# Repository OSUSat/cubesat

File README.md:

# Oregon State University (OSU) AIAA OSUSat/SCRT Climate Science CubeSat

Welcome to the central repository for the **OSUSat Climate Science CubeSat** project. This repository contains the hardware designs, firmware, and documentation for the sub-systems comprising the satellite.

---

## Mission Context & Goals

The **OSUSat Climate Science CubeSat** is a low-Earth orbit (LEO) satellite designed to capture high-resolution imagery and scientific data for climate science research. 

### Mission Objectives

1. **Earth Observations**: Capture multispectral or high-resolution imagery using a dual-camera payload to study surface health, atmospheric conditions, cloud formations.
2. **Reliable Power Delivery (EPS)**: Harvest solar power from 6 body-mounted solar panels, manage charge for 4x 18650 Li-ion batteries, and distribute and regulate power rails to prevent overcurrent/overvoltage events.
3. **Command & Telemetry (OBC)**: Orchestrate system operations, manage communication buses (CANBus, UART, I2C, SPI), process ground commands, and monitor satellite health.

---

## System Architecture

The satellite is divided into five primary subsystems interconnected via a shared backplane connector (exposing power rails and UART/CAN control buses):

```mermaid
graph TD
    Solar[Solar Panels & Batteries] --> EPS[Electrical Power System - EPS]

    EPS -->|Power| OBC[On-Board Computer - OBC]
    EPS -->|Power| Payload[Science Camera Payload]
    EPS -->|Power| ADCS[Attitude Determination & Control - ADCS]
    EPS -->|Power| Comms[UHF Communications]

    OBC <-->|Control Bus| EPS
    OBC <-->|Control Bus| Payload
    OBC <-->|Control Bus| ADCS
    OBC <-->|Control Bus| Comms

    Comms <-->|Radio Link| Ground[Ground Station]
```

### 1. Electrical Power System (EPS)

* **Microcontroller**: NXP S32K3 Series / STM32L496xx (ARM Cortex-M4)
* **Responsibilities**:
    * Solar energy harvesting with Maximum Power Point Tracking (MPPT).
    * Battery charge/discharge management (2 independent packs of 2x 18650 cells).
    * Voltage regulation (3.3V & 5V rails) with software-controllable load switches.
    * Fast hardware-level and software-level overcurrent protection.
    * Hardware watchdog monitoring.
    * Broad mission context management using the MCU

### 2. On-Board Computer (OBC)

* **Microcontroller**: Main MCU + STM32H743xx (ARM Cortex-M7)
* **Responsibilities**:
    * Master command parsing and state management.
    * Health heartbeats and telemetry collection.
    * Orbital calculations and scheduling payload imaging windows.
    * Ground station radio communication interface.

### 3. Payload

* **Processor**: Raspberry Pi Compute Module 4 (CM4)
* **Responsibilities**:
    * High-speed dual-camera scientific imaging.
    * Actuator/motor driver control (e.g., lens shutters, filter wheels) (V1 Only).
    * Image compression and storage before downlink.

### 4. Attitude Determination and Control System (ADCS)

* **Responsibilities**: Detumbling the spacecraft, aligning the imaging payload to nadir pointing, and tracking target orientations.

### 5. UHF Communications (Comms)

* **Responsibilities**: Uplinking commands and telemetry requests from ground stations, and downlinking collected science data and telemetry beacons.

---

## Repository Structure

The project uses a versioned directory structure separating hardware and firmware iterations:

```
.
├── .github/                     # GitHub Workflows & Issue/PR Templates
│   └── workflows/
│       ├── build_and_docs.yml   # CI/CD action defining the pipeline
│       └── build_and_test.sh    # Dynamic build script runner
│
├── adcs/                        # Attitude Determination and Control System
│   ├── v1/
│   └── v2/
│
├── eps/                         # Electrical Power System Subsystem
│   ├── v1/                      # Version 1 (Prototype Model)
│   │   ├── firmware/            # STM32L4 firmware (CMake, CUnit tests, mocks)
│   │   ├── hardware/            # KiCad schematic, layout, symbols, & footprints
│   │   └── documentation/       # Doxygen, Sphinx configuration & spec files
│   ├── v2/                      # Version 2 (Placeholder for v2 development)
│   └── documentation/           # Bootflows, subsystem specifications, & kickoff info
│
├── obc/                         # On-Board Computer Subsystem
│   ├── v1/                      # Version 1 (Prototype Model)
│   │   ├── firmware/            # STM32H7 firmware (CMake)
│   │   ├── hardware/            # KiCad schematic and layout
│   │   └── tests/               # Pico-based LoRa packet transmission test
│   ├── v2/                      # Version 2 (Placeholder for v2 development)
│   └── documentation/           # OBC specific documentation
│
├── payload/                     # Science Camera Payload
│   ├── v1/                      # Version 1 (Prototype Model)
│   │   └── hardware/            # KiCad CM4 baseboard schematic and layout
│   ├── v2/                      # Version 2 (Placeholder for v2 development)
│   └── documentation/           # Payload specific documentation
│
├── comms/                       # UHF Communications Subsystem (Planned)
│   ├── v1/
│   └── v2/
│
└── documentation/               # Global guidelines & Quality Assurance process
    ├── checklists/              # Bringup, layout, schematic & firmware service templates
    └── design_guidelines/       # Writing ATPs, Hardware Design, HITL, Polling/Interrupts
```

---

## Getting Started & Building

### 1. Prerequisite Toolchains

Ensure you have the following installed on your host system:
* **ARM Cross Compiler**: `gcc-arm-none-eabi`
* **Build System Tools**: `cmake`, `make`, `g++`
* **Documentation Generators**: `doxygen`, Python 3 + `sphinx`

### 2. Fetching Submodules

This repository utilizes submodules (such as `osusat/core` and `osusat/messaging`). Clone with submodules or initialize them:
```bash
git submodule update --init --recursive
```

### 3. Hardware Development & KiCad Templates

To create new expansion / daughterboard hardware designs in KiCad, symlink the shared template directory to your local KiCad user template path:

- **Linux**:
  ```bash
  mkdir -p ~/.local/share/kicad/10.0/template
  ln -sf /path/to/cubesat/repo/shared/kicad/templates/test_board ~/.local/share/kicad/10.0/template/test_board
  ```
- **Windows (PowerShell)**:
  ```powershell
  New-Item -ItemType Directory -Force -Path "$env:APPDATA\kicad\10.0\template"
  New-Item -ItemType SymbolicLink -Path "$env:APPDATA\kicad\10.0\template\test_board" -Target "C:\path\to\cubesat\repo\shared\kicad\templates\test_board"
  ```

Once symlinked, open KiCad, click **File → New Project from Template...**, select the **User Templates** tab, and choose **OSUSat Backplane Test Board Template**.

For full manual setup options and details, see [shared/kicad/README.md](./shared/kicad/README.md).

### 4. Compilation Guide

#### Building for the ARM Target (e.g., EPS v1)

To build the firmware binaries to flash onto the MCU:

```bash
cd eps/v1/firmware
cmake -B build_arm -S . -DCMAKE_TOOLCHAIN_FILE=arm-none-eabi-toolchain.cmake
cmake --build build_arm
```

*Outputs: `.elf`, `.hex`, and `.bin` files will be generated under `build_arm/`.*

#### Building Host Tests / Hardware-in-the-Loop (HITL) Mocks

To build and execute unit tests on your local machine:

```bash
cd eps/v1/firmware
cmake -B build_hitl -S . -DTARGET_ARCH=HOST -DBUILD_HITL=ON
cmake --build build_hitl
cd build_hitl && ctest --output-on-failure
```

---

## CI/CD Pipeline

The repository uses a generalized GitHub Actions workflow:
* **Scope-Based Execution**: Uses git diffs to detect which subsystem version has been modified (e.g. `eps/v1/` vs `obc/v1/`) and builds only the affected firmware.
* **Continuous Integration**: Runs host-based CTests automatically to verify changes.
* **Documentation Deployments**: Generates Doxygen API listings and Sphinx documentation on successful builds. Pull Requests automatically receive a comment with links to Pages-hosted previews of the documentation.

---

## Quality Assurance & Contributions

Before submitting a Pull Request, contributors must follow the project's QA procedures found in `/documentation`:

1. **Issue Checkout:** Before work or contributions begin, ensure your changes are encapsulated by an issue in the GitHub project
2. **Design Guidelines:** For any and all changes, follow the [design guidelines.](./documentation/design_guidelines/)
3. **Design Reviews**: Complete the [Schematic Review Checklist](./documentation/checklists/schematic_review.md) and [Layout Review Checklist](./documentation/checklists/layout_review.md) checklists before fabricating PCBs.
4. **Firmware Guidelines**: Adhere to the [HITL Guidelines](./documentation/design_guidelines/hitl.md) and [Keeping the HAL Policy Free](./documentation/design_guidelines/keeping_the_hal_policy_free.md) design rules.
5. **Acceptance Tests**: All hardware deliverables require a formal [ATP (Acceptance Test Procedure)](./documentation/design_guidelines/writing_atps.md).

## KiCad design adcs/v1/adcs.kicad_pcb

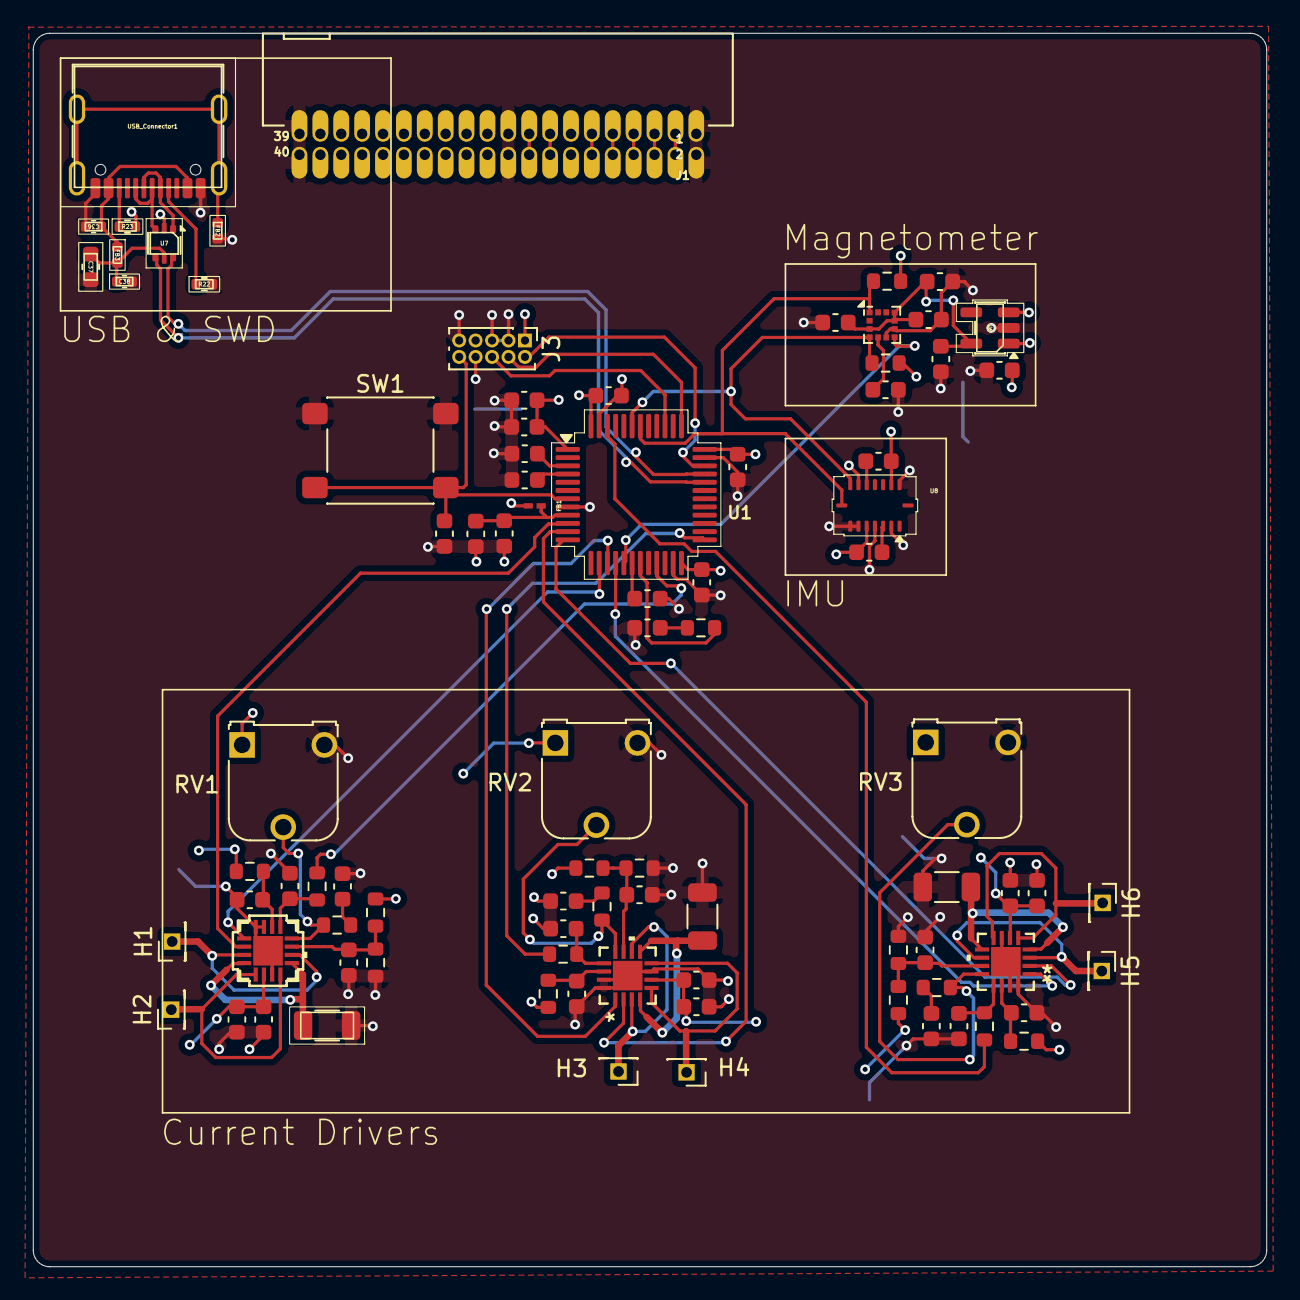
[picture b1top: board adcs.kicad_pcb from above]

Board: 4 copper layers, 75.0 x 75.0 mm, 88 parts (0 on the bottom side), 68 nets.

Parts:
C1: 4.7u; C_0603_1608Metric
C2, C3: 10p; C_0603_1608Metric
C4, C5: 20p; C_0603_1608Metric
C6, C8, C9, C11, C19, C20, C39, C40, C41: 100n; C_0603_1608Metric
C7: 0.1uF; C_0603_1608Metric
C10, C18, C34, C35, C37: 1u; C_0603_1608Metric
C12, C22, C28: 1n; C_0603_1608Metric
C13, C23, C29: 10n; C_0603_1608Metric
C14, C15, C24, C25, C30, C31: 22n; C_0603_1608Metric
C16, C26, C32: 2.2u; C_0603_1608Metric
C17, C27, C33: 22u; C_0603_1608Metric
C21: 220n; C_0603_1608Metric
C36: 10n; C_0402_1005Metric
C38: 100n; C_0402_1005Metric
FB1: 120R; IND_BLM03_0201_MUR
FB2, FB3: 120R; L_0402_1005Metric
H1, H2, H3, H4, H5, H6: MountingHole_Pad; PinHeader_1x01_P1.27mm_Vertical
J1: Conn_02x20_Counter_Clockwise; J-SAMTEC-TFM-120-X1-XXX-D-RA
J3: Conn_ARM_JTAG_SWD_10; PinHeader_2x05_P1.00mm_Vertical
R1: 390; R_0603_1608Metric
R2, R6, R10, R14, R16, R20: 1k; R_0603_1608Metric
R3, R11, R17: 10k; R_0603_1608Metric
R4, R5, R12, R13, R18, R19: 18k; R_0603_1608Metric
R7, R15, R21: 330m; R_1206_3216Metric
R8, R9: 4.7k; R_0603_1608Metric
R22, R23: 5.1k; R_0402_1005Metric
RV1, RV2, RV3: R_Potentiometer_Trim_US; Potentiometer_Runtron_RM-065_Vertical
SW1: SW_Push; SW_SPST_PTS645Sx43SMTR92
U1: STM32L4Q5CGTx; LQFP-48_7x7mm_P0.5mm
U2, U4, U5: STSPIN250; VFQFPN16_STSPIN_STM
U3: LIS2MDL; LGA-12_2x2mm_P0.5mm
U6: AP2112K-1.2; SOT-23-5
U7: USBLC6-2P6; SOT-666
U8: BMI088; Bosch_LGA-16_4.5x3mm_P0.5mm_LayoutBorder7x1y_ClockwisePinNu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
USB_Connector1: USB_C_Receptacle_USB2.0_16P; USB_C_Receptacle_G-Switch_GT-USB-7010ASV

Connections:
+1V8: C18.1, C19.1, C20.1, C35.1, U3.3 (~CS), U3.9 (Vdd), U3.10 (Vdd_IO), U6.5 (VOUT)
+3V3: C1.1, C6.1, C8.1, C9.1, C16.1, C17.1, C26.1, C27.1, C32.1, C33.1, C34.1, C39.1, C40.1, C41.1, FB1.1, J1.13, J1.14, J3.1 (VTref), R2.1, R5.1, R8.1, R9.1, R10.1, R13.1, R16.1, R19.1, RV1.1, RV2.1, RV3.1, U1.1 (VBAT), U1.24 (VDD), U1.36 (VDDUSB), U1.48 (VDD), U2.6 (VS), U4.6 (VS), U5.6 (VS), U6.1 (VIN), U6.3 (EN), U8.5 (~CSB2), U8.14 (~CSB1)
/EN1: R4.2, U1.21 (PB10)
/EN2: R12.2, U1.25 (PB12)
/EN3: R18.2, U1.46 (PB9)
/I2C1_SCL: R9.2, U1.42 (PB6), U3.1 (SCL/SPC), U8.8 (SCK/SCL)
/I2C1_SDA: R8.2, U1.43 (PB7), U3.4 (SDA/SDI/SDO), U8.9 (SDI/SDA)
/Inter-Board Connector/RAIL_1_VOUT: J1.3, J1.4
/Inter-Board Connector/RAIL_2_VOUT: J1.5, J1.6
/Inter-Board Connector/RAIL_3_VOUT: J1.7, J1.8
/Inter-Board Connector/RAIL_4_VOUT: J1.9, J1.10
/Inter-Board Connector/RAIL_5_VOUT: J1.11, J1.12
/Inter-Board Connector/RAIL_7_VOUT: J1.15, J1.16
/Inter-Board Connector/RAIL_8_VOUT: J1.17, J1.18
/MNT_INT: U1.17 (PA7), U3.7 (DRDY)
/PC14-OSC32_IN: C2.1, U1.3 (PC14)
/PC15-OSC32_OUT: C3.1, U1.4 (PC15)
/PH1: U1.14 (PA4), U2.1 (PH)
/PH2: U1.15 (PA5), U4.1 (PH)
/PH3: U1.16 (PA6), U5.1 (PH)
/PWM1_TIM2_CH1: U1.10 (PA0), U2.2 (PWM)
/PWM2_TIM2_CH2: U1.11 (PA1), U4.2 (PWM)
/PWM2_TIM2_CH3: U1.12 (PA2), U5.2 (PWM)
/STSPIN Current Driver1/V_REF: C14.1, R2.2, R3.1, U2.11 (REF)
/STSPIN Current Driver2/V_REF: C24.1, R10.2, R11.1, U4.11 (REF)
/STSPIN Current Driver3/V_REF: C30.1, R16.2, R17.1, U5.11 (REF)
/SWCLK: J3.4 (SWCLK/TCK), U1.37 (PA14)
/SWDIO: J3.2 (SWDIO/TMS), U1.34 (PA13)
/SWO: J3.6 (SWO/TDO), U1.39 (PB3)
/USB-C/CC1: R22.1, USB_Connector1.A5 (CC1)
/USB-C/CC2: R23.1, USB_Connector1.B5 (CC2)
/USB-C/FB: FB2.1, USB_Connector1.SH (SHIELD)
/USB-C/PI: C36.1, FB3.1, USB_Connector1.A4 (VBUS), USB_Connector1.A9 (VBUS), USB_Connector1.B4 (VBUS), USB_Connector1.B9 (VBUS)
/USB-C/UNPROT_USB_D+: U7.3 (I/O2), USB_Connector1.A6 (D+), USB_Connector1.B6 (D+)
/USB-C/UNPROT_USB_D-: U7.1 (I/O1), USB_Connector1.A7 (D-), USB_Connector1.B7 (D-)
/USBC-D+: U1.33 (PA12), U7.6 (I/O1)
/USBC-D-: U1.32 (PA11), U7.4 (I/O2)
/VDDA: C10.1, C11.1, FB1.2, U1.9 (VDDA)
/nRST: C7.1, J3.10 (~RESET), SW1.2, U1.7 (NRST)
GND: C1.2, C2.2, C3.2, C4.2, C5.2, C6.2, C7.2, C8.2, C9.2, C10.2, C11.2, C12.2, C13.2, C14.2, C15.2, C16.2, C17.2, C18.2, C19.2, C20.2, C21.2, C22.2, C23.2, C24.2, C25.2, C26.2, C27.2, C28.2, C29.2, C30.2, C31.2, C32.2, C33.2, C34.2, C35.2, C36.2, C37.2, C38.2, C41.2, FB2.2, J1.1, J1.2, J1.19, J1.20, J1.39, J1.40, J3.3 (GND), J3.5 (GND), J3.8 (NC/TDI), J3.9 (GNDDetect), R3.2, R7.1, R11.2, R15.1, R17.2, R21.1, R22.2, R23.2, RV1.3, RV2.3, RV3.3, SW1.1, U1.8 (VSSA), U1.23 (VSS), U1.35 (VSS), U1.47 (VSS), U2.7 (GND), U2.15 (TEST0), U2.16 (TEST1), U2.17 (EPAD), U3.6 (GND), U3.8 (GND), U4.7 (GND), U4.15 (TEST0), U4.16 (TEST1), U4.17 (EPAD), U5.7 (GND), U5.15 (TEST0), U5.16 (TEST1), U5.17 (EPAD), U6.2 (GND), U7.2 (GND), U8.2 (GNDA), U8.4 (GNDA), U8.6 (GNDIO), U8.7 (PS), U8.10 (SDO2), U8.15 (SDO1), USB_Connector1.A1 (GND), USB_Connector1.A12 (GND), USB_Connector1.B1 (GND), USB_Connector1.B12 (GND)
unnamed: C4.1, R1.1
unnamed: C15.1, R6.2
unnamed: C25.1, R14.2
unnamed: C31.1, R20.2
unnamed: C5.1, U1.18 (PB0)
unnamed: R1.2, U1.19 (PB1)
unnamed: C13.1, R4.1, U2.13 (EN/FAULT)
unnamed: H1.1 (1_1), U2.3 (OUTA1), U2.10 (OUTB1)
unnamed: H2.1 (1_1), U2.5 (OUTA2), U2.8 (OUTB2)
unnamed: R7.2, U2.4 (SENSEA), U2.9 (SENSEB)
unnamed: C12.1, R5.2, U2.14 (STBY/RESET)
unnamed: R6.1, RV1.2, U2.12 (TOFF)
unnamed: C21.1, U3.5 (C1)
unnamed: C23.1, R12.1, U4.13 (EN/FAULT)
unnamed: H3.1 (1_1), U4.3 (OUTA1), U4.10 (OUTB1)
unnamed: H4.1 (1_1), U4.5 (OUTA2), U4.8 (OUTB2)
unnamed: R15.2, U4.4 (SENSEA), U4.9 (SENSEB)
unnamed: C22.1, R13.2, U4.14 (STBY/RESET)
unnamed: R14.1, RV2.2, U4.12 (TOFF)
unnamed: C29.1, R18.1, U5.13 (EN/FAULT)
unnamed: H5.1 (1_1), U5.3 (OUTA1), U5.10 (OUTB1)
unnamed: H6.1 (1_1), U5.5 (OUTA2), U5.8 (OUTB2)
unnamed: R21.2, U5.4 (SENSEA), U5.9 (SENSEB)
unnamed: C28.1, R19.2, U5.14 (STBY/RESET)
unnamed: R20.1, RV3.2, U5.12 (TOFF)
unnamed: C39.2, U8.3 (VDD)
unnamed: C40.2, U8.11 (VDDIO)
VBUS: C37.1, C38.1, FB3.2, U7.5 (VBUS)

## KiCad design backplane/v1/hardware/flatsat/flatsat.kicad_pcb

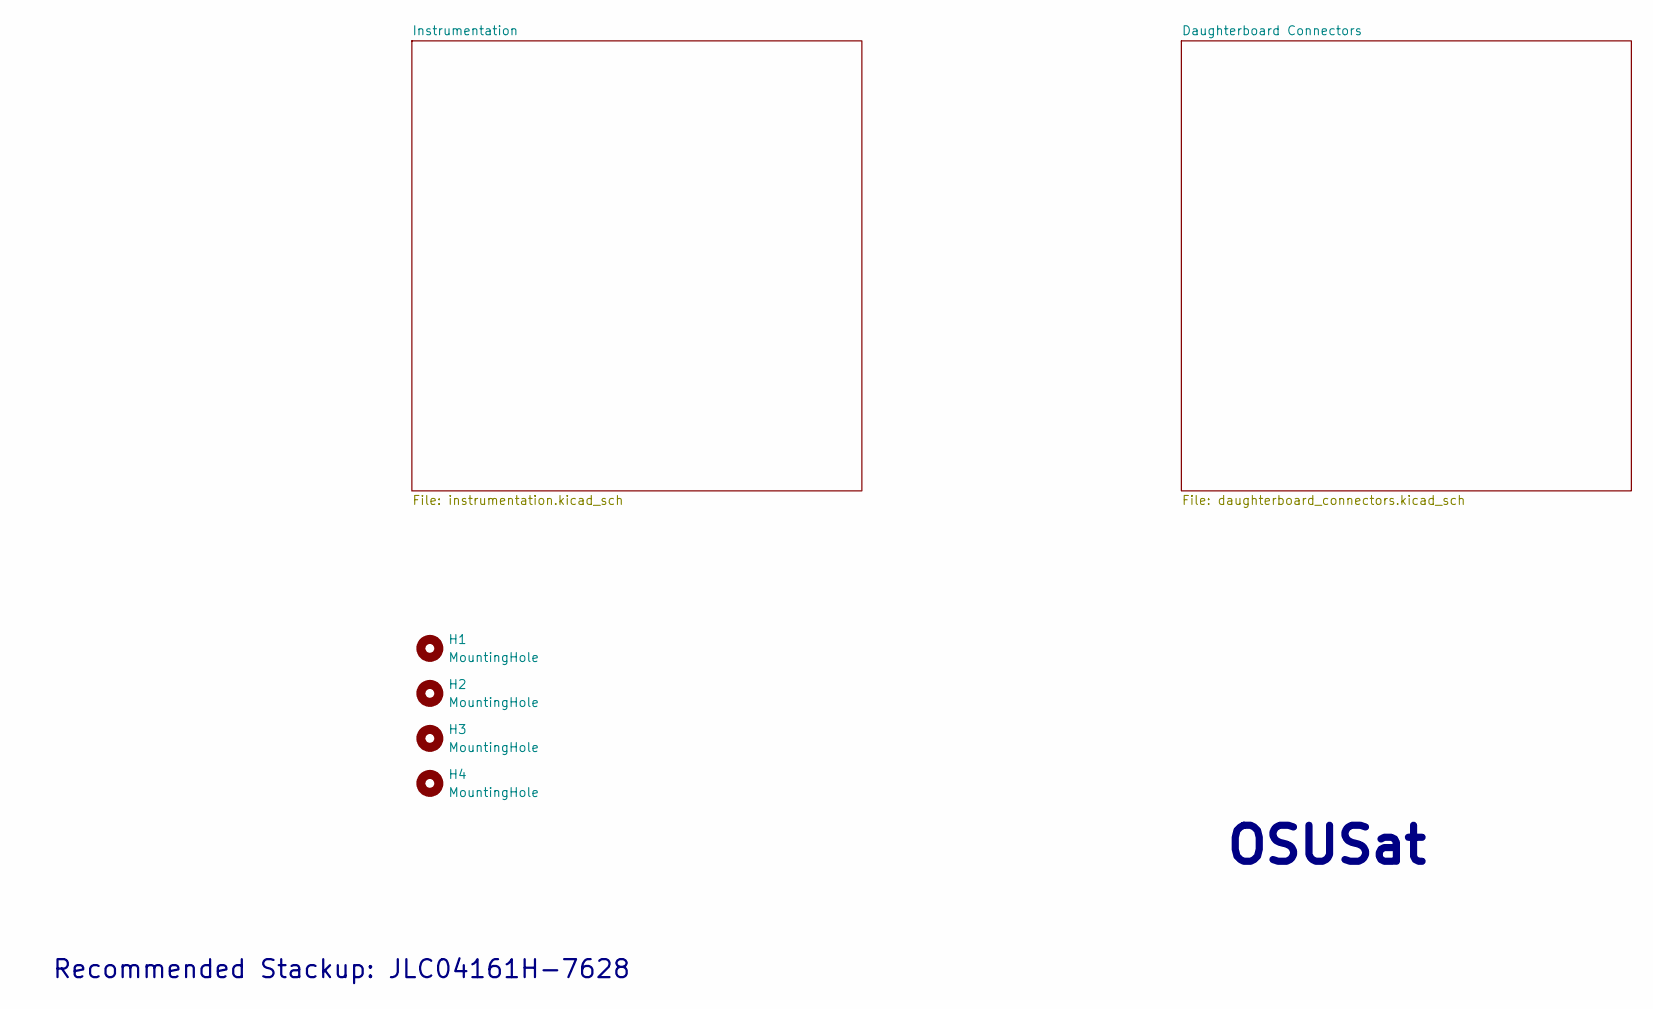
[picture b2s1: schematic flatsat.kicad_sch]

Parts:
H1, H2, H3, H4: MountingHole; MountingHole_3.2mm_M3

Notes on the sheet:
OSUSat
Recommended Stackup: JLC04161H-7628

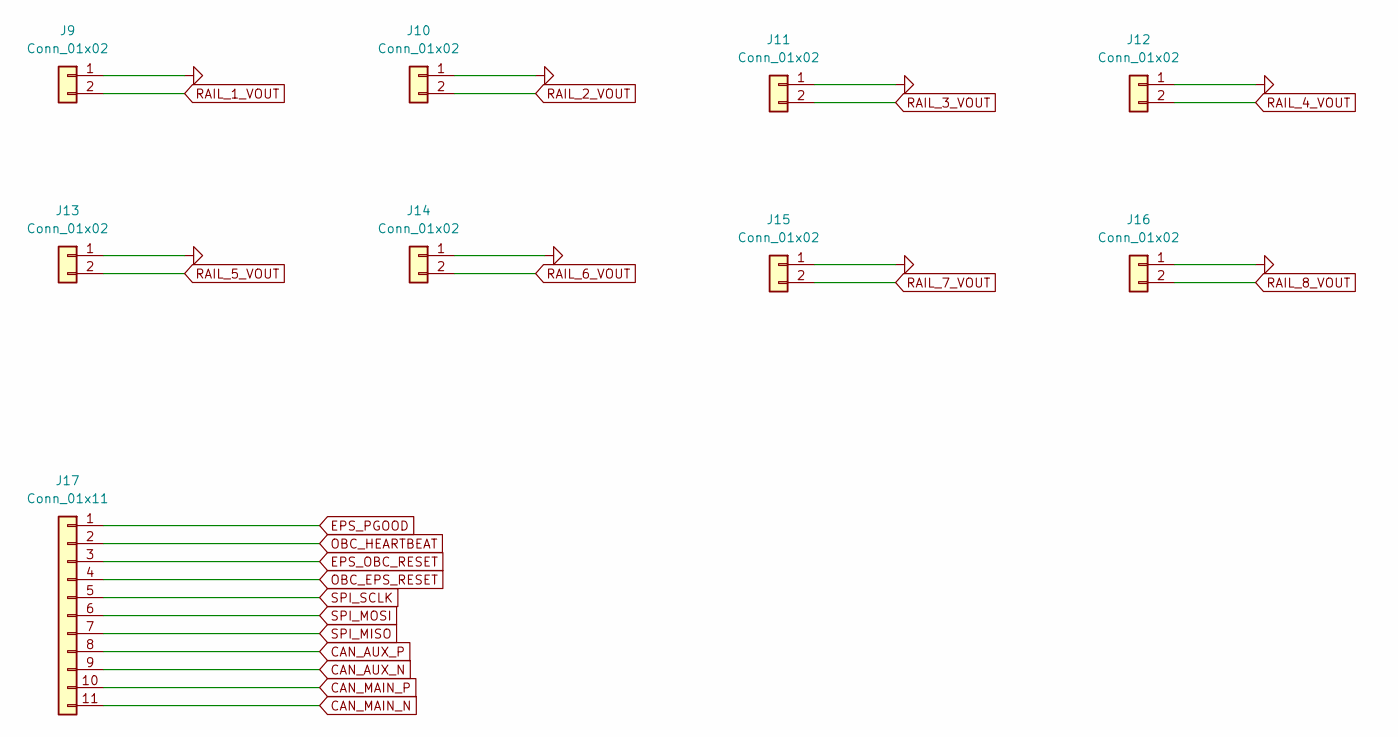
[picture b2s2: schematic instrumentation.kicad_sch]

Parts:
J9, J10, J11, J12, J13, J14, J15, J16: Conn_01x02; AMASS_XT30UPB-F_1x02_P5.0mm_Vertical
J17: Conn_01x11; PinHeader_1x11_P2.54mm_Vertical

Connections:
CAN_AUX_N: J17.9; also elsewhere on the board
CAN_AUX_P: J17.8; also elsewhere on the board
CAN_MAIN_N: J17.11; also elsewhere on the board
CAN_MAIN_P: J17.10; also elsewhere on the board
EPS_OBC_RESET: J17.3; also elsewhere on the board
EPS_PGOOD: J17.1; also elsewhere on the board
GND: J9.1, J10.1, J11.1, J12.1, J13.1, J14.1, J15.1, J16.1; also elsewhere on the board
OBC_EPS_RESET: J17.4; also elsewhere on the board
OBC_HEARTBEAT: J17.2; also elsewhere on the board
RAIL_1_VOUT: J9.2; also elsewhere on the board
RAIL_2_VOUT: J10.2; also elsewhere on the board
RAIL_3_VOUT: J11.2; also elsewhere on the board
RAIL_4_VOUT: J12.2; also elsewhere on the board
RAIL_5_VOUT: J13.2; also elsewhere on the board
RAIL_6_VOUT: J14.2; also elsewhere on the board
RAIL_7_VOUT: J15.2; also elsewhere on the board
RAIL_8_VOUT: J16.2; also elsewhere on the board
SPI_MISO: J17.7; also elsewhere on the board
SPI_MOSI: J17.6; also elsewhere on the board
SPI_SCLK: J17.5; also elsewhere on the board

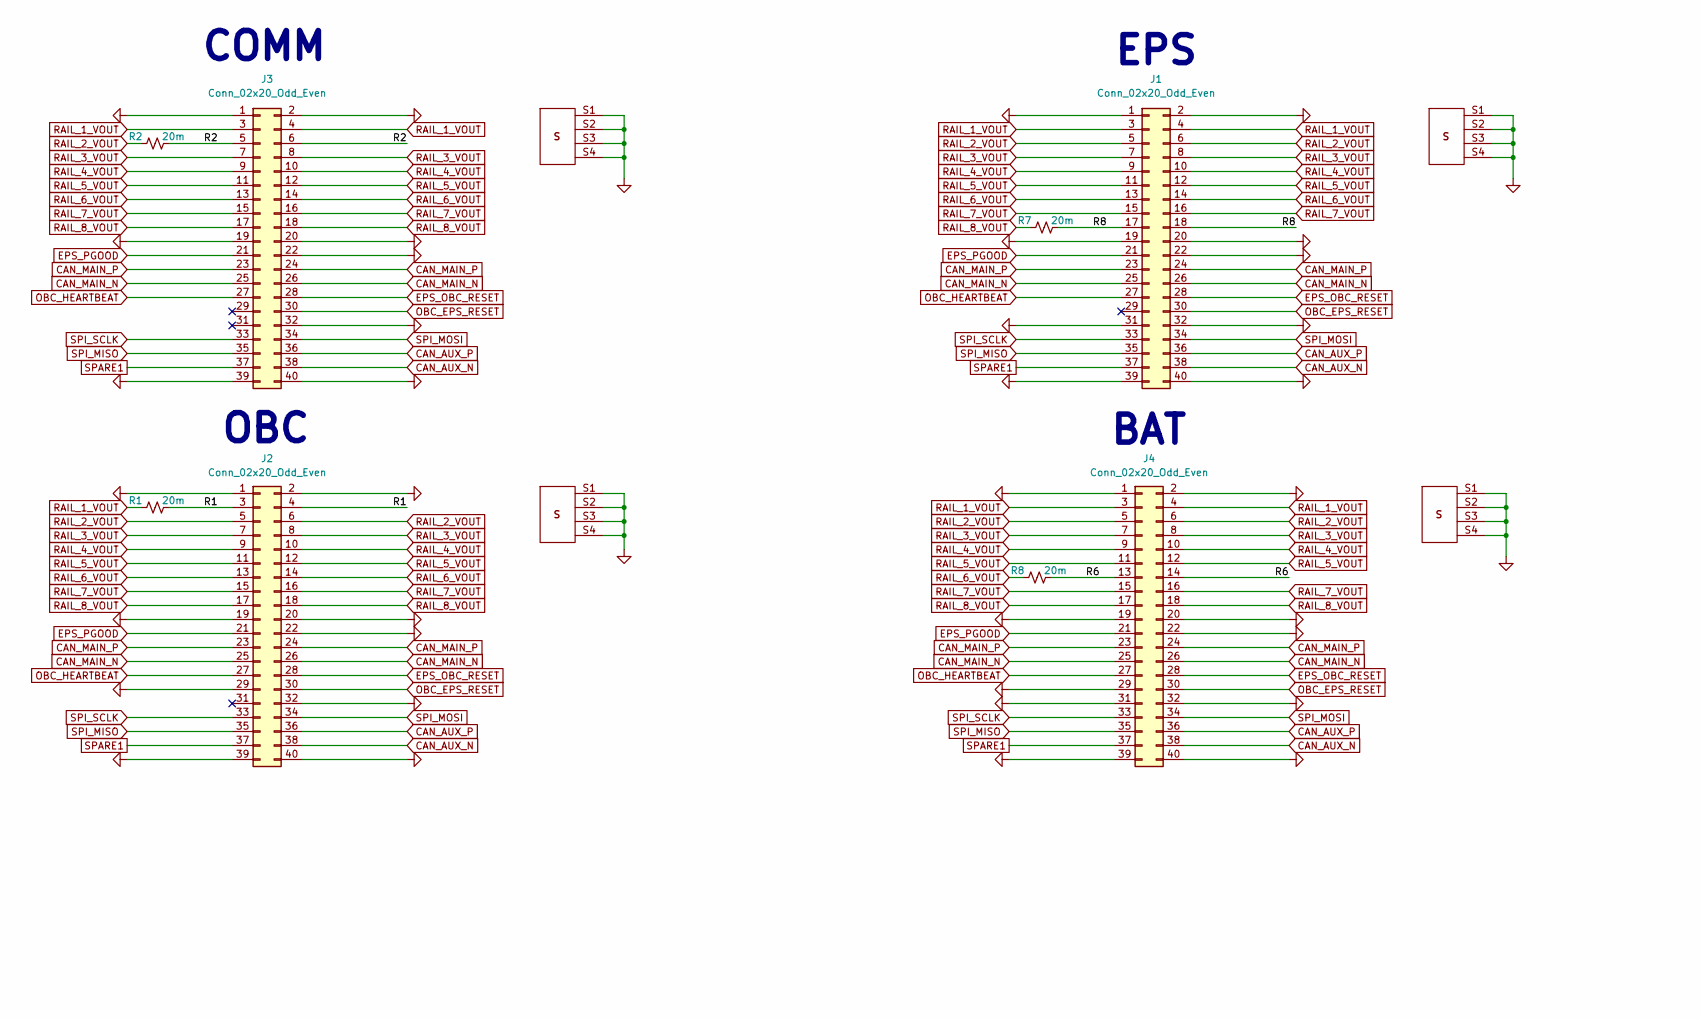
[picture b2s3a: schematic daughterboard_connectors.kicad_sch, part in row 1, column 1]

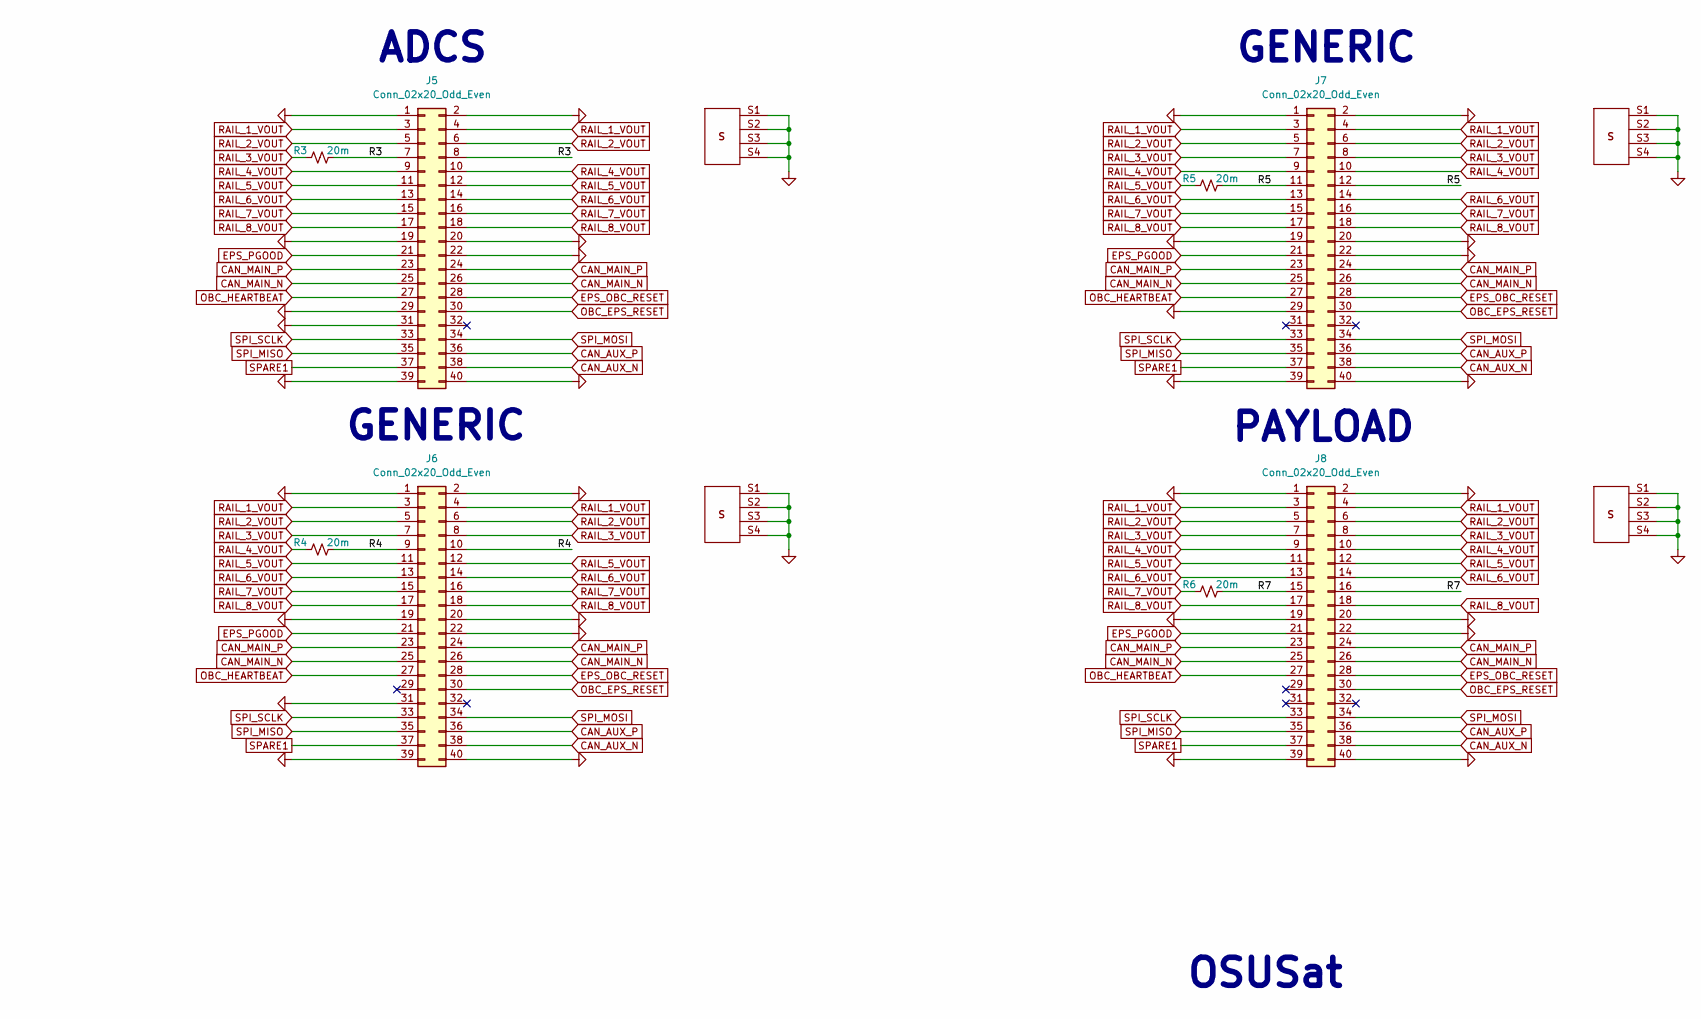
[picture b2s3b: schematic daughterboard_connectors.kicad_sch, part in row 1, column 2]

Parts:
J1, J2, J3, J4, J5, J6, J7, J8: Conn_02x20_Odd_Even; SAMTEC_SFM-120-02-L-DH-TR
R1, R2, R3, R4, R5, R6, R7, R8: 20m; R_1206_3216Metric

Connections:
/Daughterboard Connectors/R1: J2.3, J2.4, R1.2
/Daughterboard Connectors/R2: J3.5, J3.6, R2.2
/Daughterboard Connectors/R3: J5.7, J5.8, R3.2
/Daughterboard Connectors/R4: J6.9, J6.10, R4.2
/Daughterboard Connectors/R5: J7.11, J7.12, R5.2
/Daughterboard Connectors/R6: J4.13, J4.14, R8.2
/Daughterboard Connectors/R7: J8.15, J8.16, R6.2
/Daughterboard Connectors/R8: J1.17, J1.18, R7.2
CAN_AUX_N: J1.38, J2.38, J3.38, J4.38, J5.38, J6.38, J7.38, J8.38; also elsewhere on the board
CAN_AUX_P: J1.36, J2.36, J3.36, J4.36, J5.36, J6.36, J7.36, J8.36; also elsewhere on the board
CAN_MAIN_N: J1.25, J1.26, J2.25, J2.26, J3.25, J3.26, J4.25, J4.26, J5.25, J5.26, J6.25, J6.26, J7.25, J7.26, J8.25, J8.26; also elsewhere on the board
CAN_MAIN_P: J1.23, J1.24, J2.23, J2.24, J3.23, J3.24, J4.23, J4.24, J5.23, J5.24, J6.23, J6.24, J7.23, J7.24, J8.23, J8.24; also elsewhere on the board
EPS_OBC_RESET: J1.28, J2.28, J3.28, J4.28, J5.28, J6.28, J7.28, J8.28; also elsewhere on the board
EPS_PGOOD: J1.21, J2.21, J3.21, J4.21, J5.21, J6.21, J7.21, J8.21; also elsewhere on the board
GND: J1.1, J1.2, J1.19, J1.20, J1.22, J1.31, J1.32, J1.39, J1.40, J1.S1 (LC1), J1.S2 (LC2), J1.S3 (LC1), J1.S4 (LC2), J2.1, J2.2, J2.19, J2.20, J2.22, J2.29, J2.32, J2.39, J2.40, J2.S1 (LC1), J2.S2 (LC2), J2.S3 (LC1), J2.S4 (LC2), J3.1, J3.2, J3.19, J3.20, J3.22, J3.32, J3.39, J3.40, J3.S1 (LC1), J3.S2 (LC2), J3.S3 (LC1), J3.S4 (LC2), J4.1, J4.2, J4.19, J4.20, J4.22, J4.29, J4.31, J4.32, J4.39, J4.40, J4.S1 (LC1), J4.S2 (LC2), J4.S3 (LC1), J4.S4 (LC2), J5.1, J5.2, J5.19, J5.20, J5.22, J5.29, J5.31, J5.39, J5.40, J5.S1 (LC1), J5.S2 (LC2), J5.S3 (LC1), J5.S4 (LC2), J6.1, J6.2, J6.19, J6.20, J6.22, J6.31, J6.39, J6.40, J6.S1 (LC1), J6.S2 (LC2), J6.S3 (LC1), J6.S4 (LC2), J7.1, J7.2, J7.19, J7.20, J7.22, J7.29, J7.39, J7.40, J7.S1 (LC1), J7.S2 (LC2), J7.S3 (LC1), J7.S4 (LC2), J8.1, J8.2, J8.19, J8.20, J8.22, J8.39, J8.40, J8.S1 (LC1), J8.S2 (LC2), J8.S3 (LC1), J8.S4 (LC2); also elsewhere on the board
OBC_EPS_RESET: J1.30, J2.30, J3.30, J4.30, J5.30, J6.30, J7.30, J8.30; also elsewhere on the board
OBC_HEARTBEAT: J1.27, J2.27, J3.27, J4.27, J5.27, J6.27, J7.27, J8.27; also elsewhere on the board
RAIL_1_VOUT: J1.3, J1.4, J3.3, J3.4, J4.3, J4.4, J5.3, J5.4, J6.3, J6.4, J7.3, J7.4, J8.3, J8.4, R1.1; also elsewhere on the board
RAIL_2_VOUT: J1.5, J1.6, J2.5, J2.6, J4.5, J4.6, J5.5, J5.6, J6.5, J6.6, J7.5, J7.6, J8.5, J8.6, R2.1; also elsewhere on the board
RAIL_3_VOUT: J1.7, J1.8, J2.7, J2.8, J3.7, J3.8, J4.7, J4.8, J6.7, J6.8, J7.7, J7.8, J8.7, J8.8, R3.1; also elsewhere on the board
RAIL_4_VOUT: J1.9, J1.10, J2.9, J2.10, J3.9, J3.10, J4.9, J4.10, J5.9, J5.10, J7.9, J7.10, J8.9, J8.10, R4.1; also elsewhere on the board
RAIL_5_VOUT: J1.11, J1.12, J2.11, J2.12, J3.11, J3.12, J4.11, J4.12, J5.11, J5.12, J6.11, J6.12, J8.11, J8.12, R5.1; also elsewhere on the board
RAIL_6_VOUT: J1.13, J1.14, J2.13, J2.14, J3.13, J3.14, J5.13, J5.14, J6.13, J6.14, J7.13, J7.14, J8.13, J8.14, R8.1; also elsewhere on the board
RAIL_7_VOUT: J1.15, J1.16, J2.15, J2.16, J3.15, J3.16, J4.15, J4.16, J5.15, J5.16, J6.15, J6.16, J7.15, J7.16, R6.1; also elsewhere on the board
RAIL_8_VOUT: J2.17, J2.18, J3.17, J3.18, J4.17, J4.18, J5.17, J5.18, J6.17, J6.18, J7.17, J7.18, J8.17, J8.18, R7.1; also elsewhere on the board
SPARE1: J1.37, J2.37, J3.37, J4.37, J5.37, J6.37, J7.37, J8.37
SPI_MISO: J1.35, J2.35, J3.35, J4.35, J5.35, J6.35, J7.35, J8.35; also elsewhere on the board
SPI_MOSI: J1.34, J2.34, J3.34, J4.34, J5.34, J6.34, J7.34, J8.34; also elsewhere on the board
SPI_SCLK: J1.33, J2.33, J3.33, J4.33, J5.33, J6.33, J7.33, J8.33; also elsewhere on the board

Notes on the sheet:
ADCS
COMM
GENERIC
EPS
OBC
PAYLOAD
BAT
OSUSat

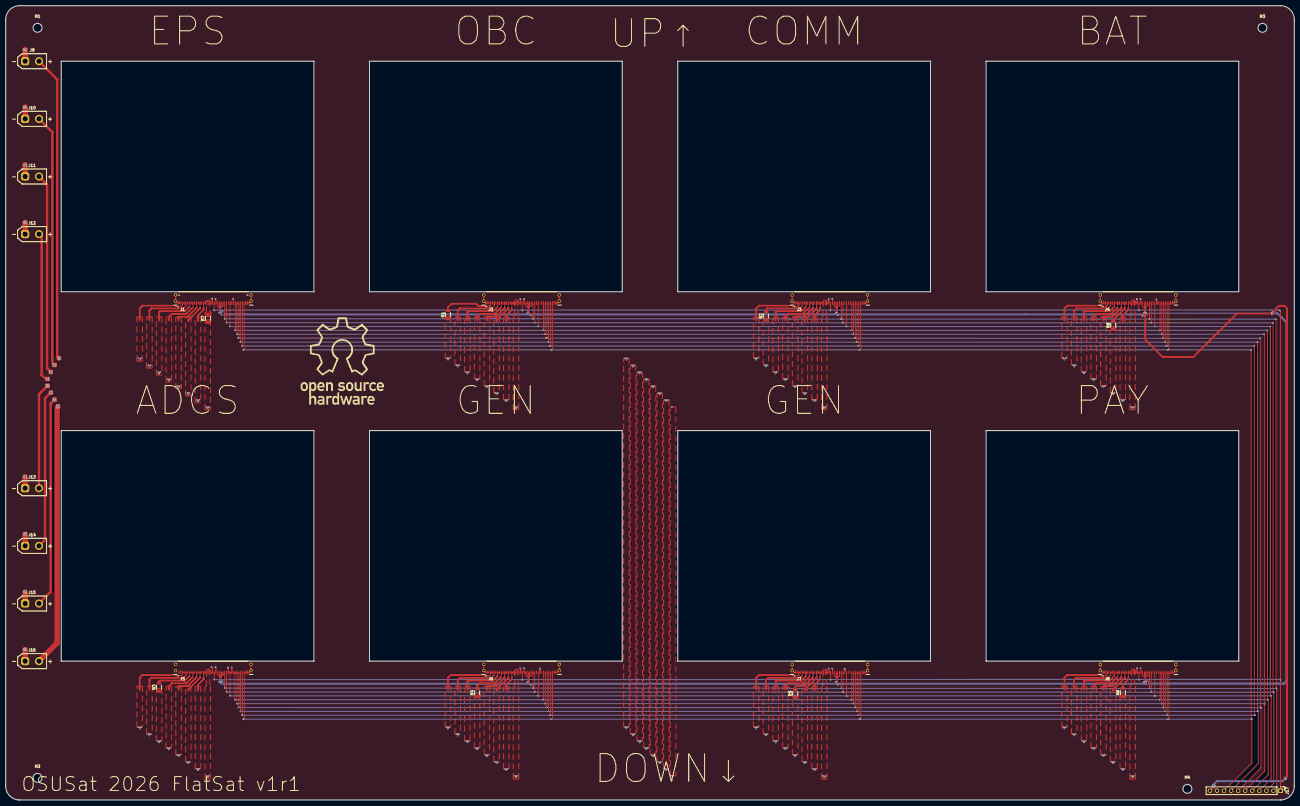
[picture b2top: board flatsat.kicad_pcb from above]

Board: 4 copper layers, 464.0 x 286.0 mm, 29 parts (0 on the bottom side), 29 nets.
